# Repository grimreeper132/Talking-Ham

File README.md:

# Talking-Ham
Open source HF, RF Valve Amplifier for HAM Radio. 

This has been started as a 4th year University Project in collaberation between Mage Control Systems and Strathclyde University

This project was taken up to the finalising the design but at time of writing (5/4/2021) it has not been written up

WARNING This device uses HV (2500 V) do not design it without prior knowledge and making a safety plan

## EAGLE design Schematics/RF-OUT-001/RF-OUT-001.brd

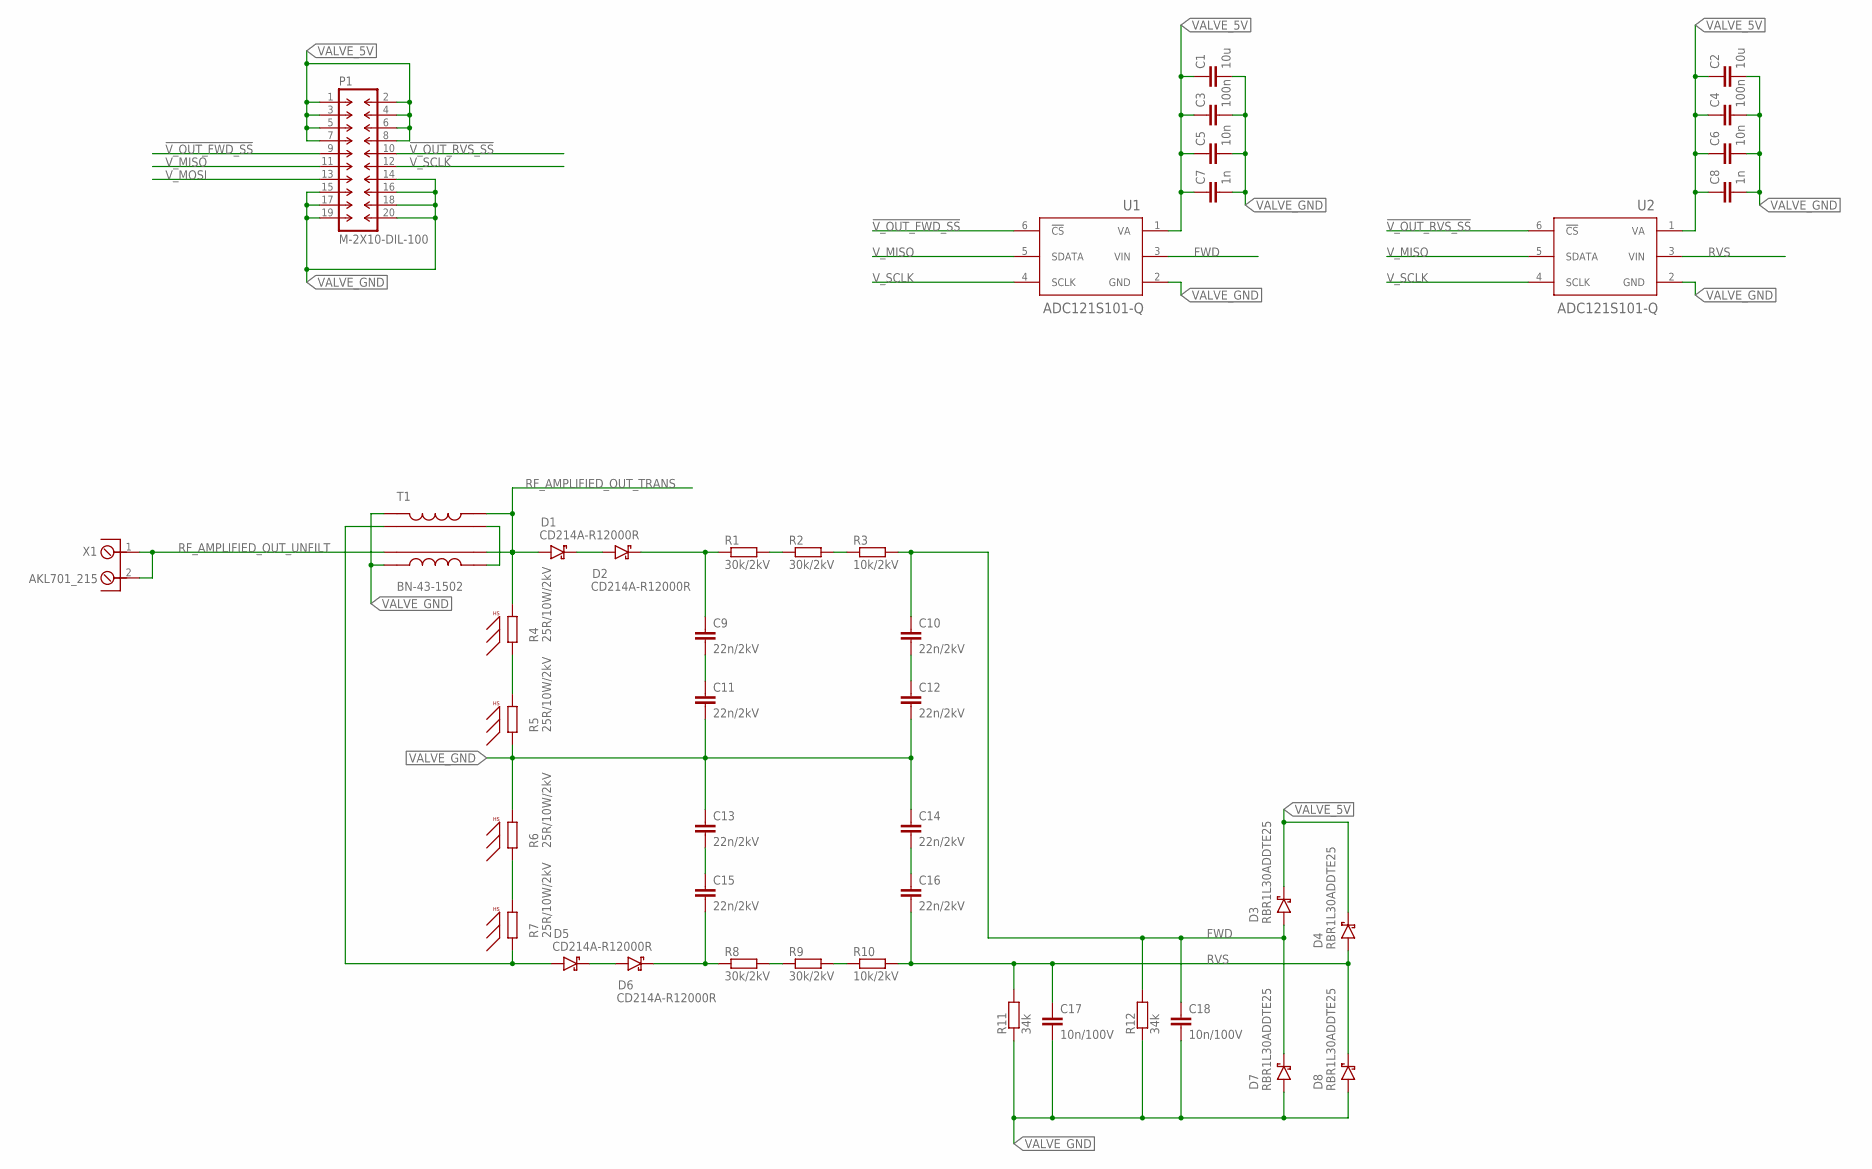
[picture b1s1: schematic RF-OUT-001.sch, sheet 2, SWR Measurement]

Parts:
C1, C2: 10u; C0805
C3, C4: 100n; C0603
C5, C6: 10n; C0603
C7, C8: 1n; C0603
C9, C10, C11, C12, C13, C14, C15, C16: 22n/2kV; C2220K
C17, C18: 10n/100V; C0603
D1, D2, D5, D6: CD214A-R12000R; SMB/DO-214AA
D3, D4, D7, D8: RBR1L30ADDTE25; SMA/DO-214AC
P1: M-2X10-DIL-100; DIL-100-2X10
R1, R2, R8, R9: 30k/2kV; 0309/10
R3, R10: 10k/2kV; 0309/10
R4, R5, R6, R7: 25R/10W/2kV; TO220ACS_WITH_WV-T220-101E
R11, R12: 34k; R0603
T1: BN-43-1502
U1, U2: ADC121S101-Q; SOT23-6
X1: AKL701_215; AKL701_2_15

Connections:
!V_OUT_FWD_SS: P1.9, U1.6 (!CS)
!V_OUT_RVS_SS: P1.10, U2.6 (!CS)
FWD: C10.1, C18.1, D3.A (ANODE), D7.C (CATHODE), R3.2, R12.2, U1.3 (VIN)
unnamed: T1.L2-2 (C2-2), T1.T1-2 (L1-2)
unnamed: R4.1, R5.2
unnamed: R6.1, R7.2
unnamed: C9.2, C11.1
unnamed: D1.C (CATHODE), D2.A (ANODE)
unnamed: C9.1, D2.C (CATHODE), R1.1
unnamed: R1.2, R2.1
unnamed: C10.2, C12.1
unnamed: R2.2, R3.1
unnamed: C13.2, C15.1
unnamed: D5.C (CATHODE), D6.A (ANODE)
unnamed: C15.2, D6.C (CATHODE), R8.1
unnamed: C14.2, C16.1
unnamed: R8.2, R9.1
unnamed: R9.2, R10.1
unnamed: D5.A (ANODE), R7.1, T1.T1-1 (L1-1)
RF_AMPLIFIED_OUT_TRANS: D1.A (ANODE), R4.2, T1.L1-2 (C1-2), T1.T2-2 (L2-2); also elsewhere on the board
RF_AMPLIFIED_OUT_UNFILT: T1.T2-1 (L2-1), X1.1, X1.2
RVS: C16.2, C17.1, D4.A (ANODE), D8.C (CATHODE), R10.2, R11.2, U2.3 (VIN)
VALVE_5V: C1.1, C2.1, C3.1, C4.1, C5.1, C6.1, C7.1, C8.1, D3.C (CATHODE), D4.C (CATHODE), P1.1, P1.2, P1.3, P1.4, P1.5, P1.6, P1.7, P1.8, U1.1 (VA), U2.1 (VA)
VALVE_GND: C1.2, C2.2, C3.2, C4.2, C5.2, C6.2, C7.2, C8.2, C11.2, C12.2, C13.1, C14.1, C17.2, C18.2, D7.A (ANODE), D8.A (ANODE), P1.14, P1.15, P1.16, P1.17, P1.18, P1.19, P1.20, R5.1, R6.2, R11.1, R12.1, T1.L1-1 (C1-1), T1.L2-1 (C2-1), U1.2 (GND), U2.2 (GND); also elsewhere on the board
V_MISO: P1.11, U1.5 (SDATA), U2.5 (SDATA)
V_MOSI: P1.13
V_SCLK: P1.12, U1.4 (SCLK), U2.4 (SCLK)

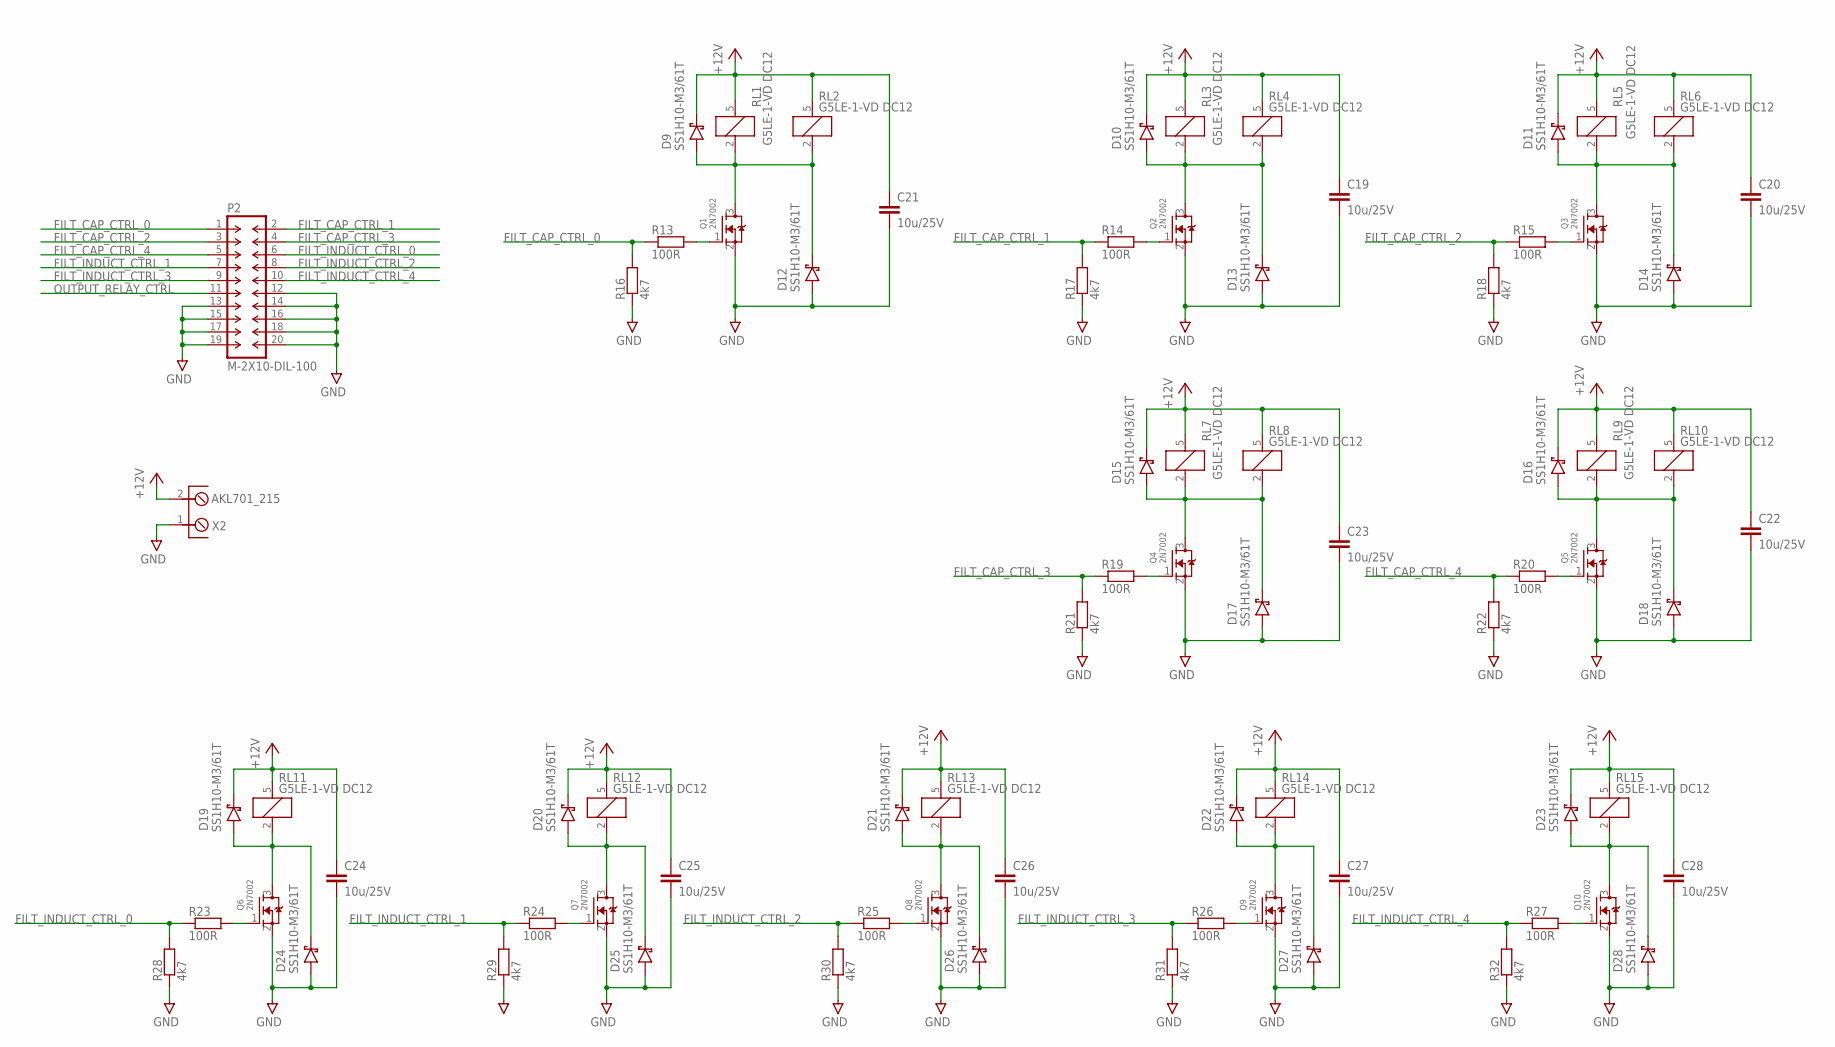
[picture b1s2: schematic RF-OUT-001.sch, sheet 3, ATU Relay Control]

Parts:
C19, C20, C21, C22, C23, C24, C25, C26, C27, C28: 10u/25V; C0805
D9, D10, D11, D12, D13, D14, D15, D16, D17, D18, D19, D20, D21, D22, D23, D24, D25, D26, D27, D28: SS1H10-M3/61T; SMA/DO-214AC
P2: M-2X10-DIL-100; DIL-100-2X10
Q1, Q2, Q3, Q4, Q5, Q6, Q7, Q8, Q9, Q10: 2N7002; SOT23
R13, R14, R15, R19, R20, R23, R24, R25, R26, R27: 100R; R0603
R16, R17, R18, R21, R22, R28, R29, R30, R31, R32: 4k7; R0603
RL1, RL2, RL3, RL4, RL5, RL6, RL7, RL8, RL9, RL10, RL11, RL12, RL13, RL14, RL15: G5LE-1-VD DC12; SPDT
X2: AKL701_215; AKL701_2_15

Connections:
+12V: C19.1, C20.1, C21.1, C22.1, C23.1, C24.1, C25.1, C26.1, C27.1, C28.1, D9.C (CATHODE), D10.C (CATHODE), D11.C (CATHODE), D15.C (CATHODE), D16.C (CATHODE), D19.C (CATHODE), D20.C (CATHODE), D21.C (CATHODE), D22.C (CATHODE), D23.C (CATHODE), RL1.5, RL2.5, RL3.5, RL4.5, RL5.5, RL6.5, RL7.5, RL8.5, RL9.5, RL10.5, RL11.5, RL12.5, RL13.5, RL14.5, RL15.5, X2.2; also elsewhere on the board
FILT_CAP_CTRL_0: P2.1, R13.1, R16.2
FILT_CAP_CTRL_1: P2.2, R14.1, R17.2
FILT_CAP_CTRL_2: P2.3, R15.1, R18.2
FILT_CAP_CTRL_3: P2.4, R19.1, R21.2
FILT_CAP_CTRL_4: P2.5, R20.1, R22.2
FILT_INDUCT_CTRL_0: P2.6, R23.1, R28.2
FILT_INDUCT_CTRL_1: P2.7, R24.1, R29.2
FILT_INDUCT_CTRL_2: P2.8, R25.1, R30.2
FILT_INDUCT_CTRL_3: P2.9, R26.1, R31.2
FILT_INDUCT_CTRL_4: P2.10, R27.1, R32.2
GND: C19.2, C20.2, C21.2, C22.2, C23.2, C24.2, C25.2, C26.2, C27.2, C28.2, D12.A (ANODE), D13.A (ANODE), D14.A (ANODE), D17.A (ANODE), D18.A (ANODE), D24.A (ANODE), D25.A (ANODE), D26.A (ANODE), D27.A (ANODE), D28.A (ANODE), P2.12, P2.13, P2.14, P2.15, P2.16, P2.17, P2.18, P2.19, P2.20, Q1.2 (S), Q2.2 (S), Q3.2 (S), Q4.2 (S), Q5.2 (S), Q6.2 (S), Q7.2 (S), Q8.2 (S), Q9.2 (S), Q10.2 (S), R16.1, R17.1, R18.1, R21.1, R22.1, R28.1, R29.1, R30.1, R31.1, R32.1, X2.1; also elsewhere on the board
unnamed: D9.A (ANODE), D12.C (CATHODE), Q1.3 (D), RL1.2, RL2.2
unnamed: Q1.1 (G), R13.2
unnamed: D10.A (ANODE), D13.C (CATHODE), Q2.3 (D), RL3.2, RL4.2
unnamed: Q2.1 (G), R14.2
unnamed: D11.A (ANODE), D14.C (CATHODE), Q3.3 (D), RL5.2, RL6.2
unnamed: Q3.1 (G), R15.2
unnamed: D15.A (ANODE), D17.C (CATHODE), Q4.3 (D), RL7.2, RL8.2
unnamed: Q4.1 (G), R19.2
unnamed: D16.A (ANODE), D18.C (CATHODE), Q5.3 (D), RL9.2, RL10.2
unnamed: Q5.1 (G), R20.2
unnamed: D19.A (ANODE), D24.C (CATHODE), Q6.3 (D), RL11.2
unnamed: Q6.1 (G), R23.2
unnamed: D20.A (ANODE), D25.C (CATHODE), Q7.3 (D), RL12.2
unnamed: Q7.1 (G), R24.2
unnamed: D21.A (ANODE), D26.C (CATHODE), Q8.3 (D), RL13.2
unnamed: Q8.1 (G), R25.2
unnamed: D22.A (ANODE), D27.C (CATHODE), Q9.3 (D), RL14.2
unnamed: Q9.1 (G), R26.2
unnamed: D23.A (ANODE), D28.C (CATHODE), Q10.3 (D), RL15.2
unnamed: Q10.1 (G), R27.2
OUTPUT_RELAY_CTRL: P2.11; also elsewhere on the board

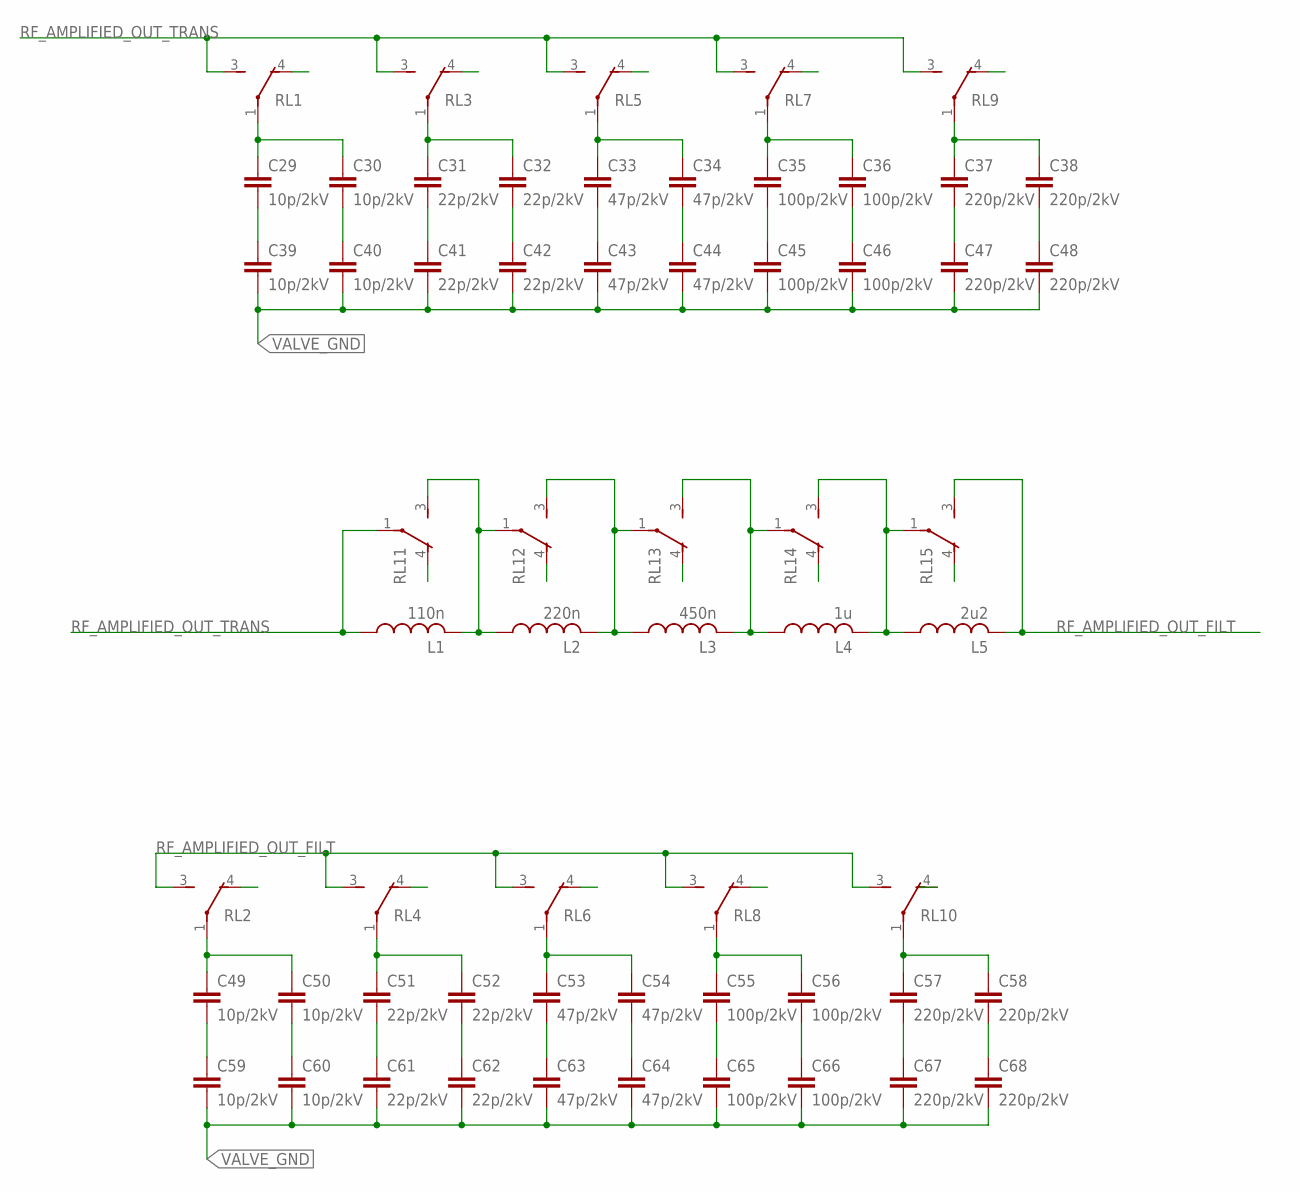
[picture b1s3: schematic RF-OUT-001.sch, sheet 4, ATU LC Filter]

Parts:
C29, C30, C39, C40, C49, C50, C59, C60: 10p/2kV; C050-055X075
C31, C32, C41, C42, C51, C52, C61, C62: 22p/2kV; C050-055X075
C33, C34, C43, C44, C53, C54, C63, C64: 47p/2kV; C050-055X075
C35, C36, C45, C46, C55, C56, C65, C66: 100p/2kV; C050-075X075
C37, C38, C47, C48, C57, C58, C67, C68: 220p/2kV; C050-075X075
L1: 110n; T80-6
L2: 220n; T80-6
L3: 450n; T80-6
L4: 1u; T80-6
L5: 2u2; T80-6
RL1, RL2, RL3, RL4, RL5, RL6, RL7, RL8, RL9, RL10, RL11, RL12, RL13, RL14, RL15: G5LE-1-VD DC12; SPDT

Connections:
unnamed: C29.1, C30.1, RL1.1
unnamed: C37.1, C38.1, RL9.1
unnamed: C49.1, C50.1, RL2.1
unnamed: C51.1, C52.1, RL4.1
unnamed: C53.1, C54.1, RL6.1
unnamed: C55.1, C56.1, RL8.1
unnamed: C29.2, C39.1
unnamed: C32.2, C42.1
unnamed: C30.2, C40.1
unnamed: C34.2, C44.1
unnamed: C36.2, C46.1
unnamed: C38.2, C48.1
unnamed: C31.2, C41.1
unnamed: C33.2, C43.1
unnamed: C35.2, C45.1
unnamed: C37.2, C47.1
unnamed: C57.1, C58.1, RL10.1
unnamed: C52.2, C62.1
unnamed: C50.2, C60.1
unnamed: C54.2, C64.1
unnamed: C56.2, C66.1
unnamed: C58.2, C68.1
unnamed: C49.2, C59.1
unnamed: C51.2, C61.1
unnamed: C53.2, C63.1
unnamed: C55.2, C65.1
unnamed: C57.2, C67.1
unnamed: C33.1, C34.1, RL5.1
unnamed: C35.1, C36.1, RL7.1
unnamed: C31.1, C32.1, RL3.1
unnamed: L4.2, L5.1, RL14.3, RL15.1
unnamed: L3.2, L4.1, RL13.3, RL14.1
unnamed: L2.2, L3.1, RL12.3, RL13.1
unnamed: L1.2, L2.1, RL11.3, RL12.1
RF_AMPLIFIED_OUT_FILT: L5.2, RL2.3, RL4.3, RL6.3, RL8.3, RL10.3, RL15.3; also elsewhere on the board
RF_AMPLIFIED_OUT_TRANS: L1.1, RL1.3, RL3.3, RL5.3, RL7.3, RL9.3, RL11.1; also elsewhere on the board
VALVE_GND: C39.2, C40.2, C41.2, C42.2, C43.2, C44.2, C45.2, C46.2, C47.2, C48.2, C59.2, C60.2, C61.2, C62.2, C63.2, C64.2, C65.2, C66.2, C67.2, C68.2; also elsewhere on the board

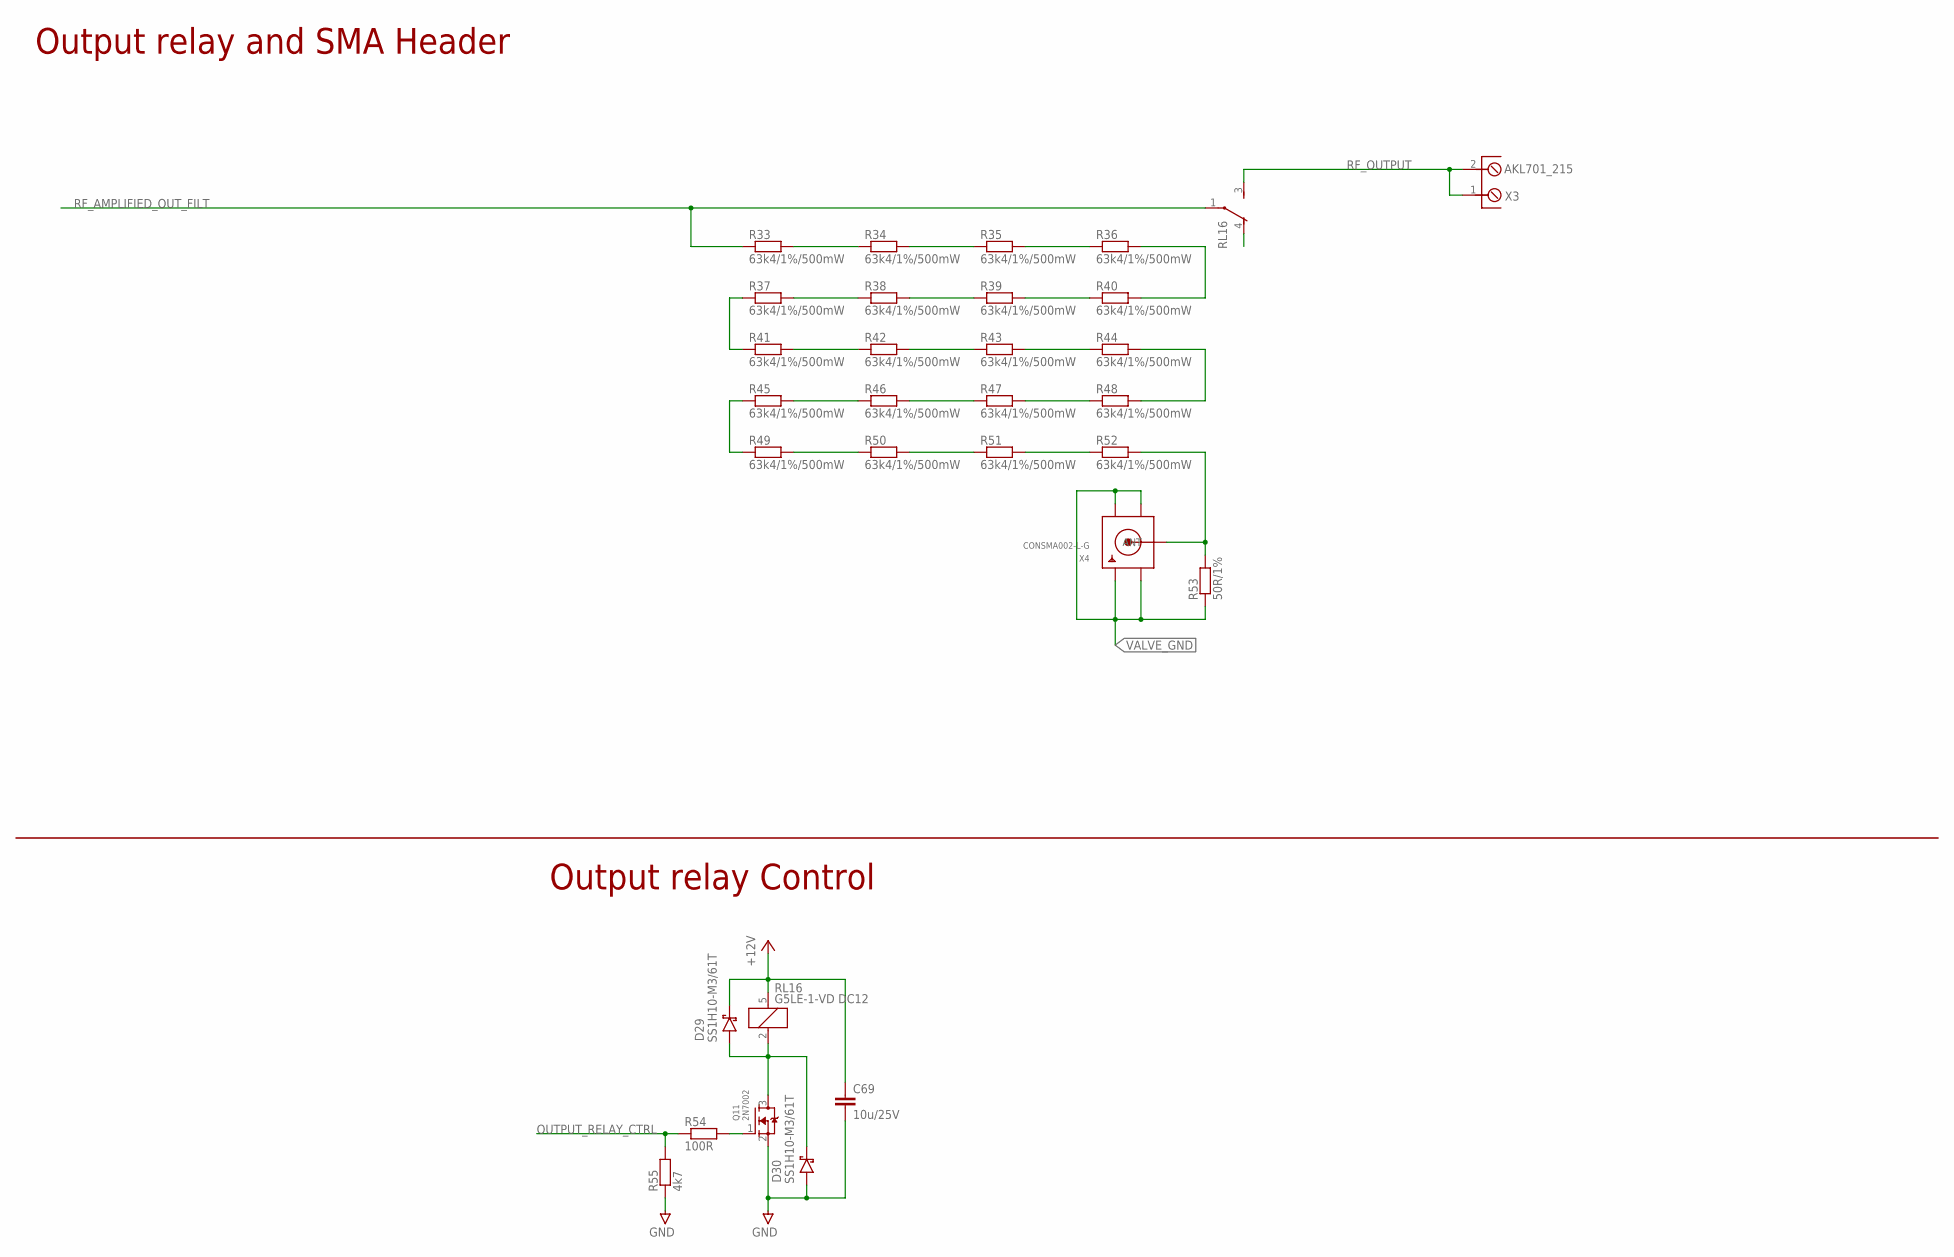
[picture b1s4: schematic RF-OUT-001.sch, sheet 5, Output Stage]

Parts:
C69: 10u/25V; C0805
D29, D30: SS1H10-M3/61T; SMA/DO-214AC
Q11: 2N7002; SOT23
R33, R34, R35, R36, R37, R38, R39, R40, R41, R42, R43, R44, R45, R46, R47, R48, R49, R50, R51, R52: 63k4/1%/500mW; R0805
R53: 50R/1%; R0603
R54: 100R; R0603
R55: 4k7; R0603
RL16: G5LE-1-VD DC12; SPDT
X3: AKL701_215; AKL701_2_15
X4: CONSMA002-L-G; SMA90_DIP

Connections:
+12V: C69.1, D29.C (CATHODE), RL16.5; also elsewhere on the board
GND: C69.2, D30.A (ANODE), Q11.2 (S), R55.1; also elsewhere on the board
unnamed: R52.2, R53.2, X4.ANTENNA (ANT)
unnamed: R33.2, R34.1
unnamed: R37.1, R41.1
unnamed: R37.2, R38.1
unnamed: R45.1, R49.1
unnamed: R41.2, R42.1
unnamed: R45.2, R46.1
unnamed: R49.2, R50.1
unnamed: R34.2, R35.1
unnamed: R38.2, R39.1
unnamed: R42.2, R43.1
unnamed: R46.2, R47.1
unnamed: R50.2, R51.1
unnamed: R35.2, R36.1
unnamed: R39.2, R40.1
unnamed: R43.2, R44.1
unnamed: R47.2, R48.1
unnamed: R51.2, R52.1
unnamed: R36.2, R40.2
unnamed: R44.2, R48.2
unnamed: D29.A (ANODE), D30.C (CATHODE), Q11.3 (D), RL16.2
unnamed: Q11.1 (G), R54.2
OUTPUT_RELAY_CTRL: R54.1, R55.2; also elsewhere on the board
RF_AMPLIFIED_OUT_FILT: R33.1, RL16.1; also elsewhere on the board
RF_OUTPUT: RL16.3, X3.1, X3.2
VALVE_GND: R53.1, X4.GND1, X4.GND2, X4.GND3, X4.GND4; also elsewhere on the board

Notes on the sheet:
Output relay Control
Output relay and SMA Header

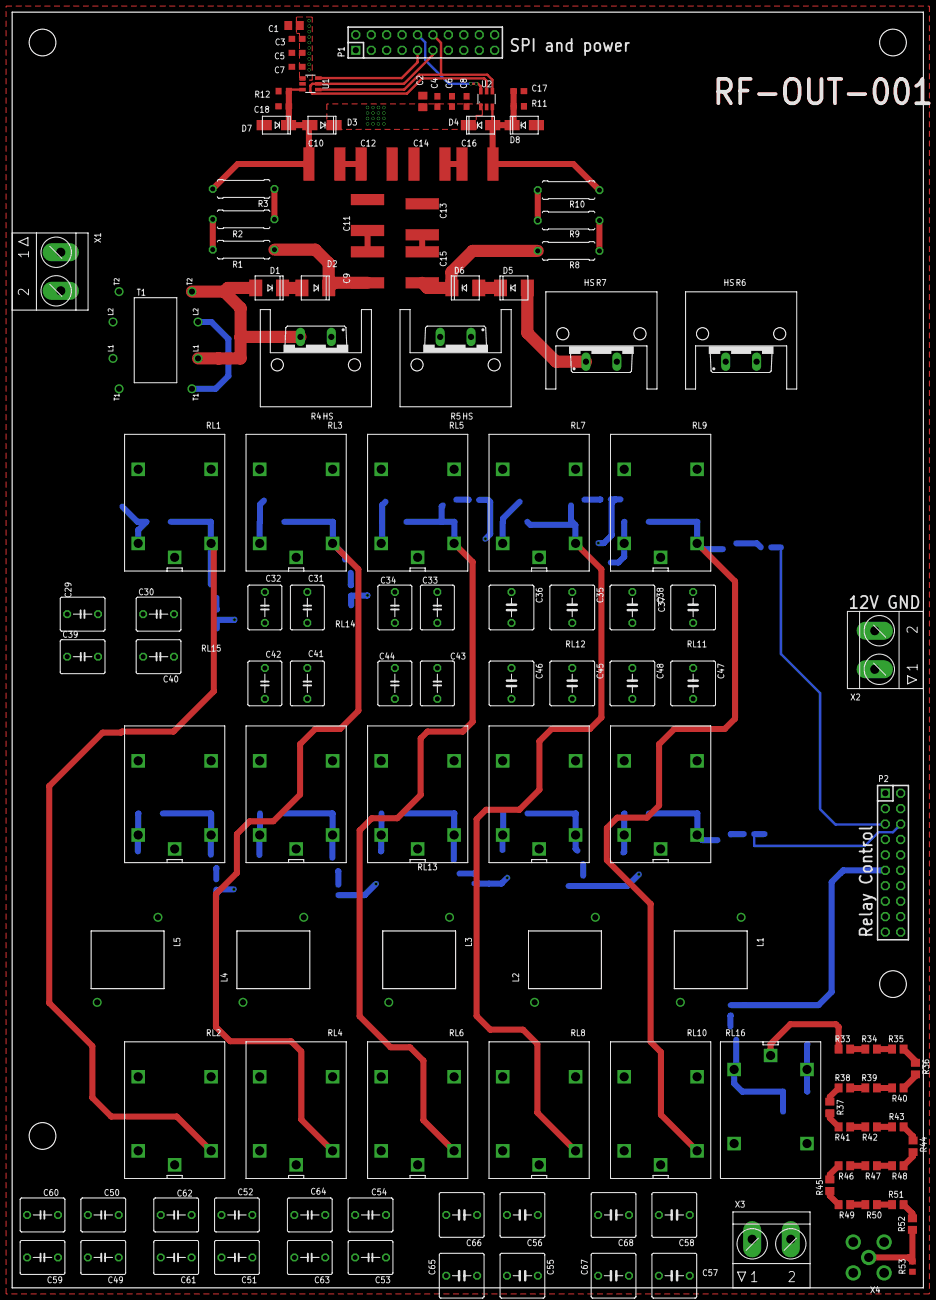
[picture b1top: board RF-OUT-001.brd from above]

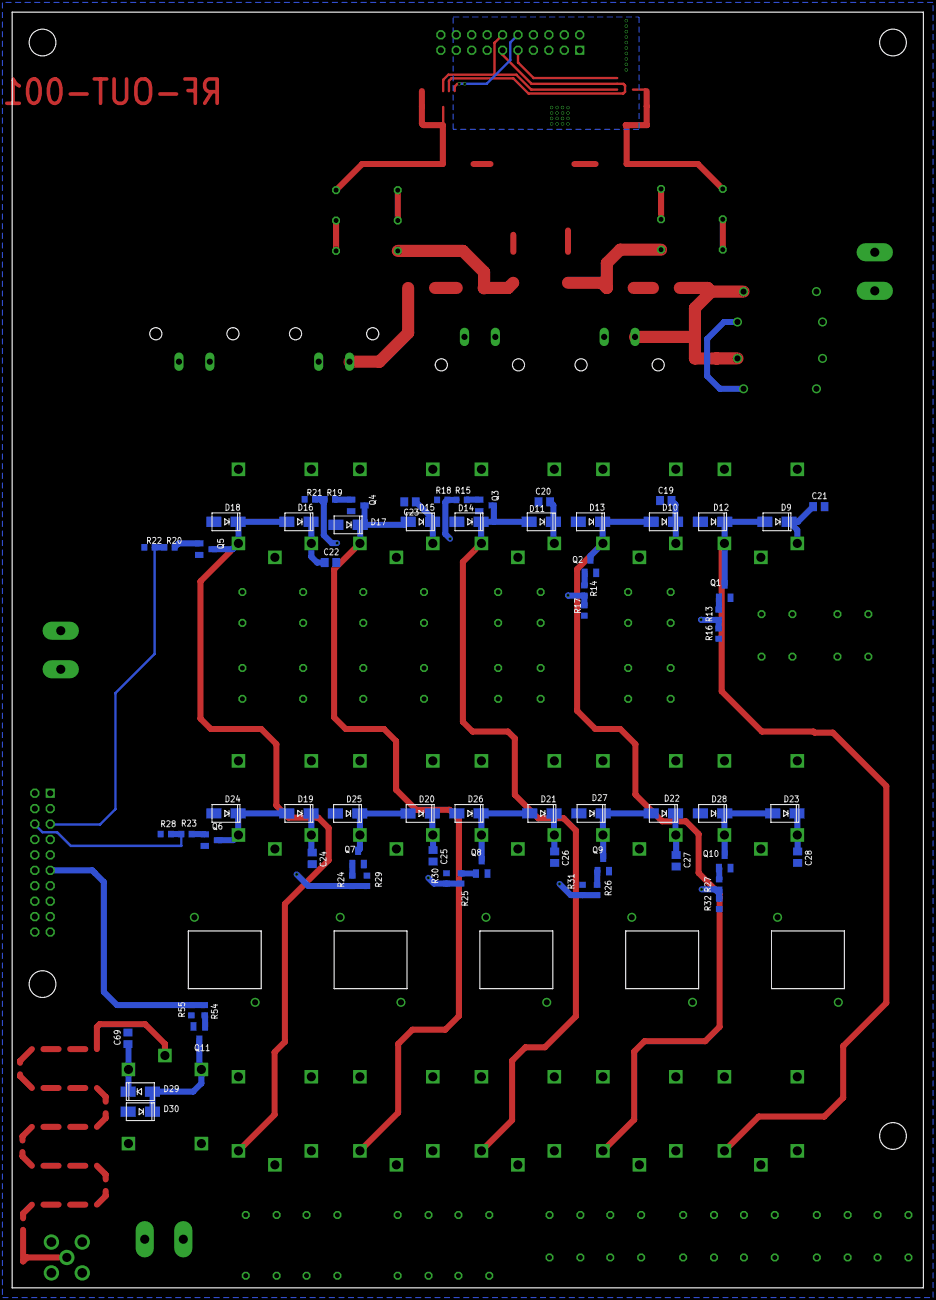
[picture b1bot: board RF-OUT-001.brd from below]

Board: 4 copper layers, 150.0 x 210.0 mm, 195 parts (66 on the bottom side), 117 nets.

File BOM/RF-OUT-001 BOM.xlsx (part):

|  |  | Board ID |  |  | Engineer |  |  | Project |  |  | Job NO.
 |  |  | Revision | 1 |  | Approval |  |  | Customer |  |  | Boards Required | 1
 | (don't touch)
 | Component Number | Type Colour | Schematic Ref | Quantity | Spare Parts | Description | Footprint | Value | Tolerance | Manufacturer | Manufacturer Part Number | Preferred Supplier | Order-code | Alternate Supplier | Alt Order-Code | Unit/Reel Price | Packaging | Reel QTY | Stock | Price per board | Total Price (all boards) | Order Quantity | Order Price
 | 0 | 1 | C1, C2, C81, C82, C83, C84, C85, C86, C87, C88, C89, C90, C91 | 13 |  | X5R Ceramic Capacitor | C0805 | 10u/25V |  | Samsung Electro-Mechanics | CL21A106KAYNNNE | Mouser | 187-CL21A106KAYNNNE |  |  | 0.13700000000000001 | Cut Tape | 1000 |  | 1.7810000000000001 | 1.7810000000000001 | 13 | 1.7810000000000001
 | 1 | 1 | C19, C24 | 2 |  | Ceramic Disc Capacitors | D5.5mm | 22p/2kV |  | TDK | CC45SL3DD220JYGNA | Mouser | 810-CC45SL3DD220JYGN | Digi-Key | 445-CC45SL3DD220JYGNA-ND | 0.26600000000000001 | Cut Tape | 1000 |  | 0.53200000000000003 | 0.53200000000000003 | 2 | 0.53200000000000003
 | 2 | 1 | C20, C25 | 2 |  | Ceramic Disc Capacitors | D5.5mm | 10p/3kV |  | TDK | CC45SL3FD100JYGNA | Mouser | 810-CC45SL3FD100JYGN | Farnell | 3416296 | 0.26600000000000001 | Cut Tape | 1000 |  | 0.53200000000000003 | 0.53200000000000003 | 2 | 0.53200000000000003
 | 3 | 1 | C21, C26 | 2 |  | Ceramic Disc Capacitors | D5.5mm | 47p/2kV |  | TDK | CC45SL3DD470JYGNA | Mouser | 810-CC45SL3DD470JYGN | Digi-Key | 445-180992-ND | 0.221 | Cut Tape | 1000 |  | 0.442 | 0.442 | 2 | 0.442
 | 4 | 1 | C22, C28 | 2 |  | Ceramic Disc Capacitors | D5.5mm | 220p/2kV |  | TDK | CK45-B3DD221KYNNA | Mouser | 810-CK45-B3DD221NNA |  |  | 0.312 | Cut Tape | 1000 |  | 0.624 | 0.624 | 2 | 0.624
 | 5 | 1 | C23, C27 | 2 |  | Ceramic Disc Capacitors | D5.5mm | 100p/2kV |  | TDK | CK45-B3FD101KYGNA | Mouser | 810-CK45-B3FD101KYGN |  |  | 0.29699999999999999 | Cut Tape | 1000 |  | 0.59399999999999997 | 0.59399999999999997 | 2 | 0.59399999999999997
 | 6 | 1 | C3, C4 | 2 |  | X7R Ceramic Capacitor | C0603 | 100n/100V | 0.1 | Samsung Electro-Mechanics | CL10B104KC8NNNC | Mouser | 187-CL10B104KC8NNNC |  |  | 7.6999999999999999E-2 | Cut Tape | 1000 |  | 0.154 | 0.154 | 2 | 0.154
 | 7 | 1 | C5, C6, C17, C18 | 4 |  | X7R Ceramic Capacitor | C0603 | 10n/100V | 0.1 | KEMET | C0603C103K1RACTU | Mouser | 80-C0603C103K1R |  |  | 7.6999999999999999E-2 | Cut Tape | 1000 |  | 0.308 | 0.308 | 4 | 0.308
 | 8 | 1 | C7, C8 | 2 |  | C0G Ceramic Capacitor | C0603 | 1n/100V | 0.05 | Wurth Elektronik | 885012006085 | Mouser | 710-885012006085 |  |  | 7.6999999999999999E-2 | Cut Tape | 1000 |  | 0.154 | 0.154 | 2 | 0.154
 | 9 | 1 | C9, C10, C11, C12, C13, C14, C15, C16 | 8 |  | X7R Ceramic Capacitor | C2220 | 22n/2kV | 0.1 | AVX | 2220GC223KAT1A | Mouser | 581-2220GC223KAT1A |  |  | 0.82399999999999995 | Cut Tape | 1000 |  | 6.5919999999999996 | 6.5919999999999996 | 8 | 6.5919999999999996
 | 10 | 2 | R1, R2, R8, R9 | 4 |  | Metal Film Resistor | 9mm TH | 30k/3.5kV | 0.05 | Yageo | HHV-50JT-52-30K | Mouser | 603-HHV-50JT-52-30K |  |  | 0.39600000000000002 | Cut Tape | 1000 |  | 1.5840000000000001 | 1.5840000000000001 | 4 | 1.5840000000000001
 | 11 | 2 | R11, R12 | 2 |  | Thick Film Resistor | R0603 | 34k | 0.01 | Panasonic | ERJ-3EKF3402V | Mouser | 667-ERJ-3EKF3402V |  |  | 7.6999999999999999E-2 | Cut Tape | 1000 |  | 0.154 | 0.154 | 2 | 0.154
 | 12 | 2 | R13, R14, R15, R19, R20, R23, R24, R25, R26, R27, R54 | 11 |  | Thick Film Resistor | R0603 | 100R | 0.01 | Vishay/Dale | CRCW0603100RFKEAC | Mouser | 71-CRCW0603100RFKEAC |  |  | 7.6999999999999999E-2 | Cut Tape | 1000 |  | 0.84699999999999998 | 0.84699999999999998 | 11 | 0.84699999999999998
 | 13 | 2 | R16, R17, R18, R21, R22, R28, R29, R30, R31, R32, R55 | 11 |  | Thick Film Resistor | R0603 | 4k7 | 0.05 | Vishay / Dale | CRCW06034K70JNEAC | Mouser | 71-CRCW06034K70JNEAC |  |  | 7.6999999999999999E-2 | Cut Tape | 1000 |  | 0.84699999999999998 | 0.84699999999999998 | 11 | 0.84699999999999998
 | 14 | 2 | R3, R10 | 2 |  | Metal Film Resistor | 9mm TH | 10k/3.5kV | 0.05 | Yageo | HHV-50JT-52-10K | Mouser | 603-HHV-50JT-52-10K |  |  | 0.39600000000000002 | Cut Tape | 1000 |  | 0.79200000000000004 | 0.79200000000000004 | 2 | 0.79200000000000004
 | 15 | 2 | R33, R34, R35, R36, R37, R38, R39, R40, R41, R42, R43, R44, R45, R46, R47, R48,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 | 20 |  | Thick Film Resistor | R0805 | 63k4/500mW | 0.01 | Bourns | CR0805-FX-6342ELF | Mouser | 652-CR0805FX-6342ELF |  |  | 7.6999999999999999E-2 | Cut Tape | 1000 |  | 1.54 | 1.54 | 20 | 1.54
 | 16 | 2 | R4, R5, R6, R7 | 4 |  | Thick Film Resistor | TO-220 | 25R/30W/2kV |  | Bourns | PWR221T-30-25R0F | Mouser | 652-PWR221T-30-25R0F |  |  | 2.19 | Cut Tape | 1000 |  | 8.76 | 8.76 | 4 | 8.76
 | 17 | 2 | R53 | 1 |  | Thick Film Resistor | R0603 | 50R | 0.01 | Vishay / Dale | CRCW060350R0FKTA | Mouser | 71-CRCW0603-50 |  |  | 0.17599999999999999 | Cut Tape | 1000 |  | 0.17599999999999999 | 0.17599999999999999 | 1 | 0.17599999999999999
 | 18 | 3 | L1 | 1 |  | RF Inductor Toroid Core | T80-6 | 5 turns 20 AWG |  | Micrometals | T60-6 | Pace Components | link |  |  | 0.88 | Cut Tape | 1000 |  | 0.88 | 0.88 | 1 | 0.88
 | 19 | 3 | L2 | 1 |  | RF Inductor Toroid Core | T80-6 | 7 turns 20 AWG |  | Micrometals | T60-6 | Pace Components | link |  |  | 0.88 | Cut Tape | 1000 |  | 0.88 | 0.88 | 1 | 0.88
 | 20 | 3 | L3 | 1 |  | RF Inductor Toroid Core | T80-6 | 10 turns 20 AWG |  | Micrometals | T60-6 | Pace Components | link |  |  | 0.88 | Cut Tape | 1000 |  | 0.88 | 0.88 | 1 | 0.88
 | 21 | 3 | L4 | 1 |  | RF Inductor Toroid Core | T80-6 | 15 turns 20 AWG |  | Micrometals | T60-6 | Pace Components | link |  |  | 0.88 | Cut Tape | 1000 |  | 0.88 | 0.88 | 1 | 0.88
 | 22 | 3 | L5 | 1 |  | RF Inductor Toroid Core | T80-6 | 22 turns 20 AWG |  | Micrometals | T60-6 | Pace Components | link |  |  | 0.88 | Cut Tape | 1000 |  | 0.88 | 0.88 | 1 | 0.88
 | 23 | 3 | T1 | 1 |  | Ferrite Toroid Core | Custom | 2 Hole |  | Amidon | BN-43-1502 | Ebay | Link | Amidon | BN-43-1502 | 3.79 | Cut Tape | 1000 |  | 3.79 | 3.79 | 1 | 3.79
 | 24 | 4 | D1, D2, D5, D6 | 4 |  | Schottky Diode | SMB |  |  | Bourns | CD214A-R12000R | Mouser | 652-CD214A-R12000R |  |  | 0.40400000000000003 | Cut Tape | 1000 |  | 1.6160000000000001 | 1.6160000000000001 | 4 | 1.6160000000000001
 | 25 | 4 | D3, D4, D7, D8 | 4 |  | Schottky Diode | SMA | Vr 30V 30A |  | ROHM Semiconductor | RBR1L30ADDTE25 | Mouser | 755-RBR1L30ADDTE25 |  |  | 0.374 | Cut Tape | 1000 |  | 1.496 | 1.496 | 4 | 1.496
 | 26 | 4 | D9, D10, D11, D12, D13, D14, D15, D16, D17, D18, D19, D20, D21, D22, D23, D24, 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 | 22 |  | Schottky Diode | SMA | 0.62V 1A |  | Vishay General Semiconductor | SS1H10-M3/61T | Mouser | 78-SS1H10-M361T |  |  | 0.28199999999999997 | Cut Tape | 1000 |  | 6.2039999999999997 | 6.2039999999999997 | 22 | 6.2039999999999997
 | 27 | 6 | Q1, Q2, Q3, Q4, Q5, Q6, Q7, Q8, Q9, Q10, Q11 | 11 |  | N-Channel MOSFET | SOT23 |  |  | Nexperia | 2N7002NXAKR | Mouser | 771-2N7002NXAKR |  |  | 7.6999999999999999E-2 | Cut Tape | 1000 |  | 0.84699999999999998 | 0.84699999999999998 | 11 | 0.84699999999999998
 | 28 | 7 | RL1, RL2, RL3, RL4, RL5, RL6, RL7, RL8, RL9, RL10, RL11, RL12, RL13, RL14, RL15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 | 16 |  | General Purpose Relay | G5LE | SPDT |  | Omron Electronics | G5LE-1-VD DC12 | Mouser | 653-G5LE-1-VDDC12 |  |  | 1.07 | Cut Tape | 1000 |  | 17.12 | 17.12 | 16 | 17.12
 | 29 | 7 | U1, U2 | 2 |  | Analogue to Digital Convertor | SOT-23-6 | 12 bit |  | Texas Instruments | ADC121S101QIMF/NOPB | Mouser | 595-DC121S101QIMFNPB |  |  | 4.0599999999999996 | Cut Tape | 1000 |  | 8.1199999999999992 | 8.1199999999999992 | 2 | 8.1199999999999992
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

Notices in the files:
parts and their libraries:
con-headers-jp: Copyright (C) 2008, Bob Starr
Wurth_Power Magnetics_WE-HCF: Copyright: Würth Elektronik
